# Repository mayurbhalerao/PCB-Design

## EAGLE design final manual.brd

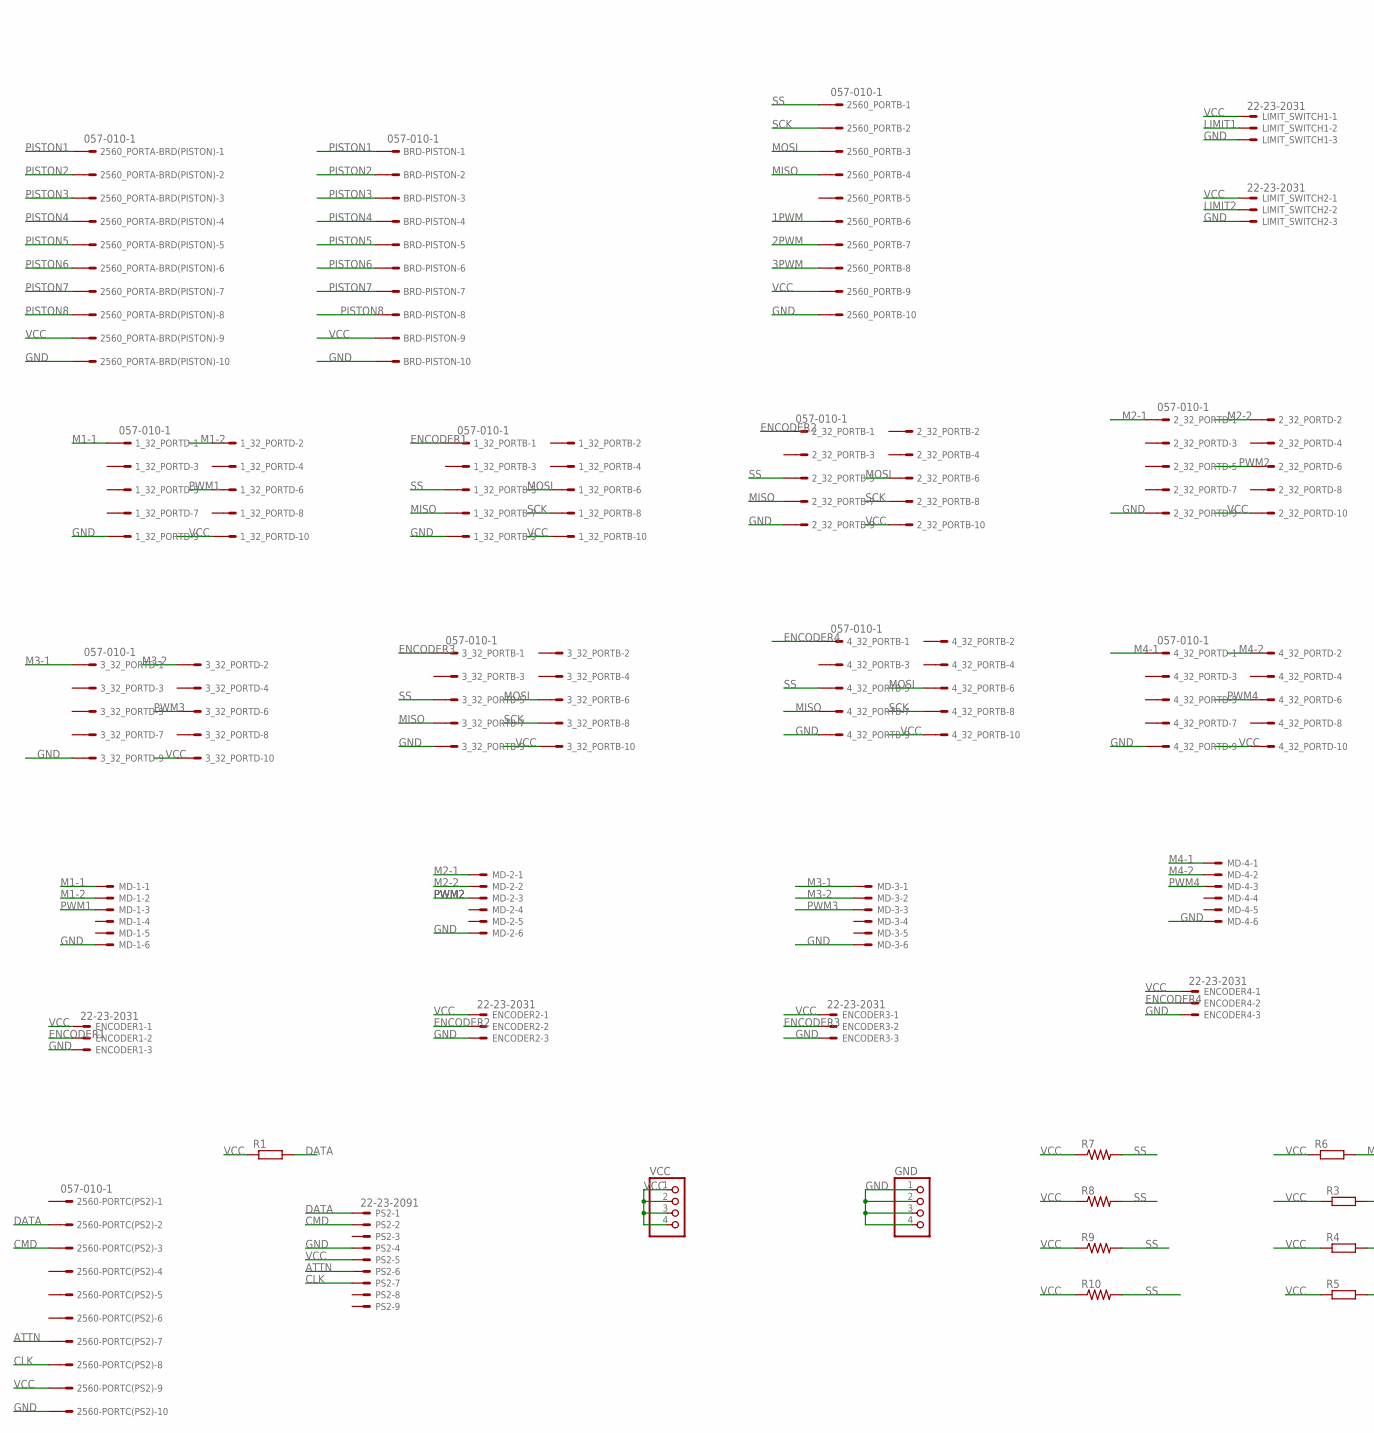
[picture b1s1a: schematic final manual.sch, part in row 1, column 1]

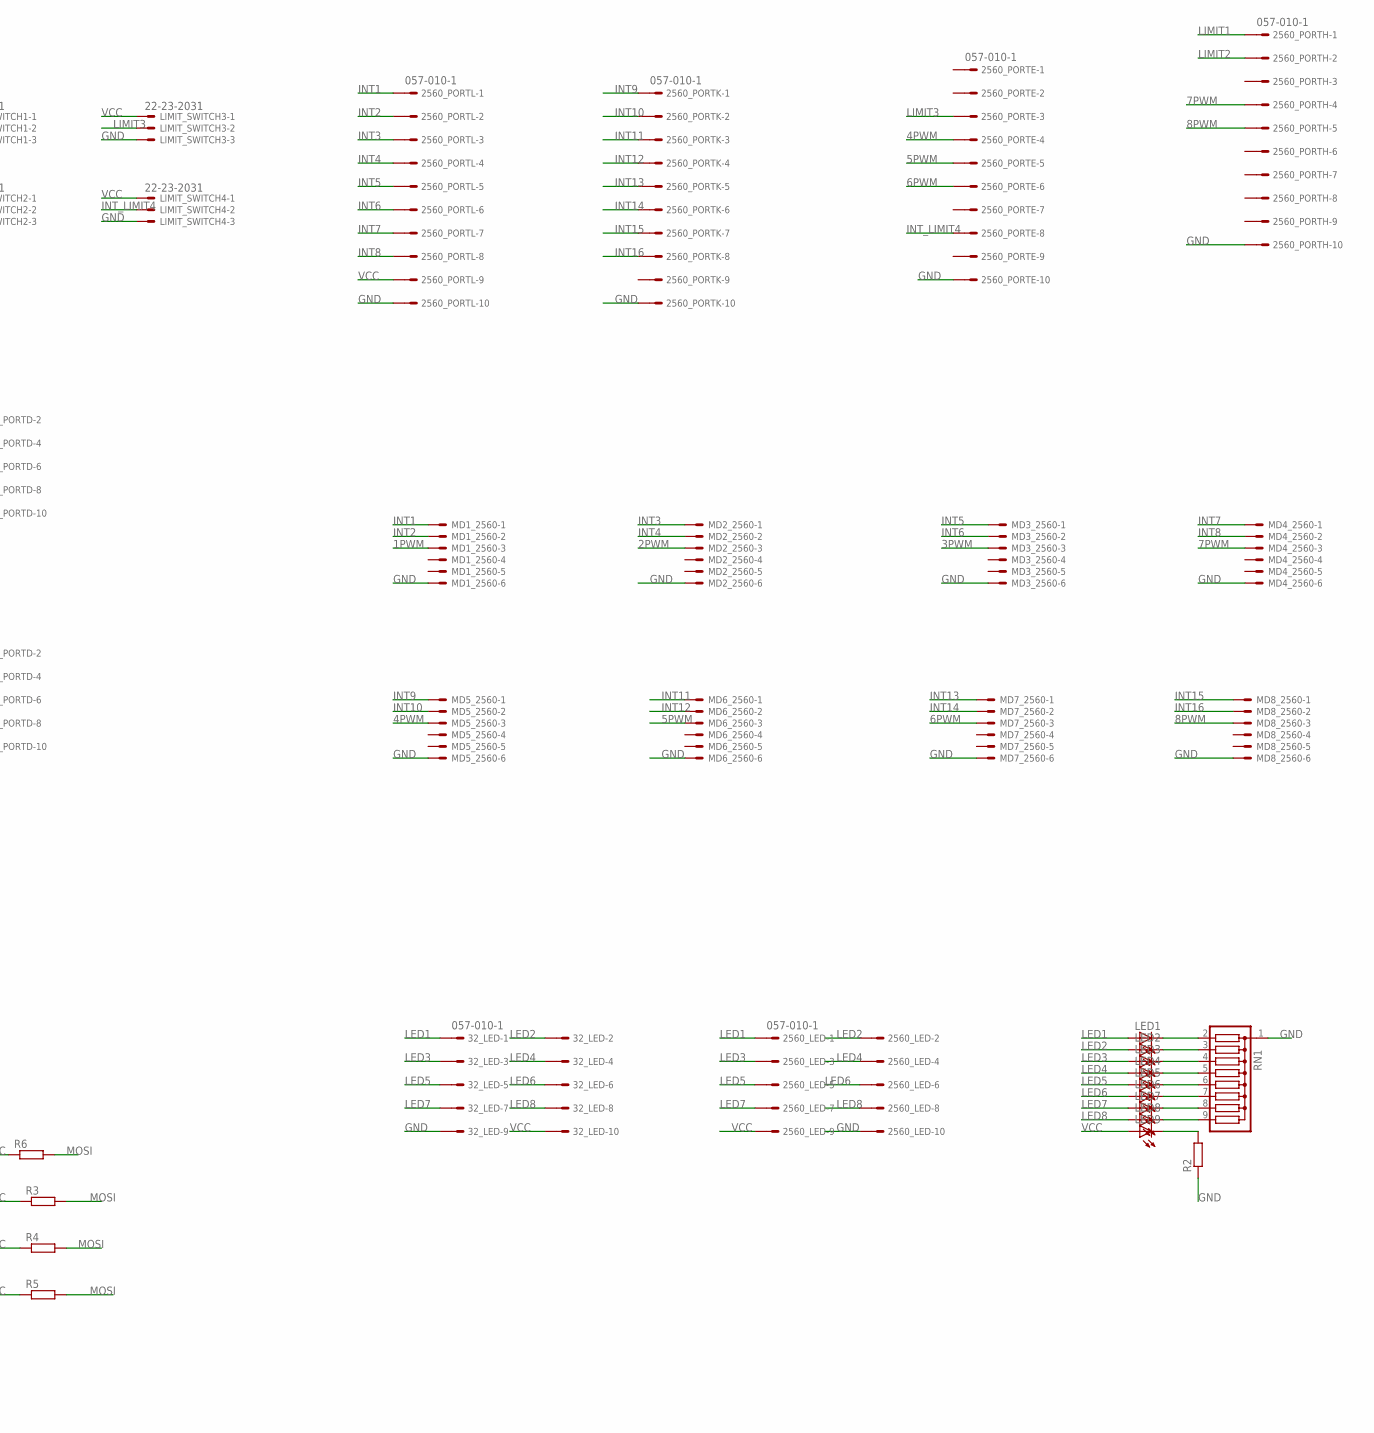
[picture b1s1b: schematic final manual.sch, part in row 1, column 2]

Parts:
1_32_PORTB, 1_32_PORTD, 2_32_PORTB, 2_32_PORTD, 3_32_PORTB, 3_32_PORTD, 4_32_PORTB, 4_32_PORTD, 32_LED, 2560-PORTC(PS2), 2560_LED, 2560_PORTA-BRD(PISTON), 2560_PORTB, 2560_PORTE, 2560_PORTH, 2560_PORTK, 2560_PORTL: 057-010-1
BRD-PISTON: 057-010-1
ENCODER1, ENCODER2, ENCODER3, ENCODER4: 22-23-2031
GND: PINHD-1X4; 1X04
LED1, LED2, LED3, LED4, LED5, LED6, LED7, LED8, LED9: LED3MM
LIMIT_SWITCH1, LIMIT_SWITCH2, LIMIT_SWITCH3, LIMIT_SWITCH4: 22-23-2031
MD1_2560, MD2_2560, MD3_2560, MD4_2560, MD5_2560, MD6_2560, MD7_2560, MD8_2560: 22-23-2061
MD-1, MD-2, MD-3, MD-4: 22-23-2061
PS2: 22-23-2091
R1, R2, R3, R4, R5, R6: R-EU_0204/7; 0204/7
R7, R8, R9, R10: R-US_0204/7; 0204/7
RN1: G08R; SIL9
VCC: PINHD-1X4; 1X04

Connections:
1PWM: 2560_PORTB.6, MD1_2560.3
2PWM: 2560_PORTB.7, MD2_2560.3
3PWM: 2560_PORTB.8, MD3_2560.3
4PWM: 2560_PORTE.4, MD5_2560.3
5PWM: 2560_PORTE.5, MD6_2560.3
6PWM: 2560_PORTE.6, MD7_2560.3
7PWM: 2560_PORTH.4, MD4_2560.3
8PWM: 2560_PORTH.5, MD8_2560.3
ATTN: 2560-PORTC(PS2).7, PS2.6
CLK: 2560-PORTC(PS2).8, PS2.7
CMD: 2560-PORTC(PS2).3, PS2.2
DATA: 2560-PORTC(PS2).2, PS2.1, R1.2
ENCODER1: 1_32_PORTB.1, ENCODER1.2
ENCODER2: 2_32_PORTB.1, ENCODER2.2
ENCODER3: 3_32_PORTB.1, ENCODER3.2
ENCODER4: 4_32_PORTB.1, ENCODER4.2
GND: 1_32_PORTB.9, 1_32_PORTD.9, 2_32_PORTB.9, 2_32_PORTD.9, 3_32_PORTB.9, 3_32_PORTD.9, 4_32_PORTB.9, 4_32_PORTD.9, 32_LED.9, 2560-PORTC(PS2).10, 2560_LED.10, 2560_PORTA-BRD(PISTON).10, 2560_PORTB.10, 2560_PORTE.10, 2560_PORTH.10, 2560_PORTK.10, 2560_PORTL.10, BRD-PISTON.10, ENCODER1.3, ENCODER2.3, ENCODER3.3, ENCODER4.3, GND.1, GND.2, GND.3, GND.4, LIMIT_SWITCH1.3, LIMIT_SWITCH2.3, LIMIT_SWITCH3.3, LIMIT_SWITCH4.3, MD1_2560.6, MD2_2560.6, MD3_2560.6, MD4_2560.6, MD5_2560.6, MD6_2560.6, MD7_2560.6, MD8_2560.6, MD-1.6, MD-2.6, MD-3.6, MD-4.6, PS2.4, R2.1, RN1.1
INT1: 2560_PORTL.1, MD1_2560.1
INT2: 2560_PORTL.2, MD1_2560.2
INT3: 2560_PORTL.3, MD2_2560.1
INT4: 2560_PORTL.4, MD2_2560.2
INT5: 2560_PORTL.5, MD3_2560.1
INT6: 2560_PORTL.6, MD3_2560.2
INT7: 2560_PORTL.7, MD4_2560.1
INT8: 2560_PORTL.8, MD4_2560.2
INT9: 2560_PORTK.1, MD5_2560.1
INT10: 2560_PORTK.2, MD5_2560.2
INT11: 2560_PORTK.3, MD6_2560.1
INT12: 2560_PORTK.4, MD6_2560.2
INT13: 2560_PORTK.5, MD7_2560.1
INT14: 2560_PORTK.6, MD7_2560.2
INT15: 2560_PORTK.7, MD8_2560.1
INT16: 2560_PORTK.8, MD8_2560.2
INT_LIMIT4: 2560_PORTE.8, LIMIT_SWITCH4.2
LED1: 32_LED.1, 2560_LED.1, LED1.A
LED2: 32_LED.2, 2560_LED.2, LED2.A
LED3: 32_LED.3, 2560_LED.3, LED3.A
LED4: 32_LED.4, 2560_LED.4, LED4.A
LED5: 32_LED.5, 2560_LED.5, LED5.A
LED6: 32_LED.6, 2560_LED.6, LED6.A
LED7: 32_LED.7, 2560_LED.7, LED7.A
LED8: 32_LED.8, 2560_LED.8, LED8.A
LIMIT1: 2560_PORTH.1, LIMIT_SWITCH1.2
LIMIT2: 2560_PORTH.2, LIMIT_SWITCH2.2
LIMIT3: 2560_PORTE.3, LIMIT_SWITCH3.2
M1-1: 1_32_PORTD.1, MD-1.1
M1-2: 1_32_PORTD.2, MD-1.2
M2-1: 2_32_PORTD.1, MD-2.1
M2-2: 2_32_PORTD.2, MD-2.2
M3-1: 3_32_PORTD.1, MD-3.1
M3-2: 3_32_PORTD.2, MD-3.2
M4-1: 4_32_PORTD.1, MD-4.1
M4-2: 4_32_PORTD.2, MD-4.2
MISO: 1_32_PORTB.7, 2_32_PORTB.7, 3_32_PORTB.7, 4_32_PORTB.7, 2560_PORTB.4
MOSI: 1_32_PORTB.6, 2_32_PORTB.6, 3_32_PORTB.6, 4_32_PORTB.6, 2560_PORTB.3, R3.2, R4.2, R5.2, R6.2
unnamed: LED1.K (C), RN1.2
unnamed: LED2.K (C), RN1.3
unnamed: LED3.K (C), RN1.4
unnamed: LED4.K (C), RN1.5
unnamed: LED5.K (C), RN1.6
unnamed: LED6.K (C), RN1.7
unnamed: LED7.K (C), RN1.8
unnamed: LED8.K (C), RN1.9
unnamed: LED9.K (C), R2.2
PISTON1: 2560_PORTA-BRD(PISTON).1, BRD-PISTON.1
PISTON2: 2560_PORTA-BRD(PISTON).2, BRD-PISTON.2
PISTON3: 2560_PORTA-BRD(PISTON).3, BRD-PISTON.3
PISTON4: 2560_PORTA-BRD(PISTON).4, BRD-PISTON.4
PISTON5: 2560_PORTA-BRD(PISTON).5, BRD-PISTON.5
PISTON6: 2560_PORTA-BRD(PISTON).6, BRD-PISTON.6
PISTON7: 2560_PORTA-BRD(PISTON).7, BRD-PISTON.7
PISTON8: 2560_PORTA-BRD(PISTON).8, BRD-PISTON.8
PWM1: 1_32_PORTD.6, MD-1.3
PWM2: 2_32_PORTD.6, MD-2.3
PWM3: 3_32_PORTD.6, MD-3.3
PWM4: 4_32_PORTD.6, MD-4.3
SCK: 1_32_PORTB.8, 2_32_PORTB.8, 3_32_PORTB.8, 4_32_PORTB.8, 2560_PORTB.2
SS: 1_32_PORTB.5, 2_32_PORTB.5, 3_32_PORTB.5, 4_32_PORTB.5, 2560_PORTB.1, R7.2, R8.2, R9.2, R10.2
VCC: 1_32_PORTB.10, 1_32_PORTD.10, 2_32_PORTB.10, 2_32_PORTD.10, 3_32_PORTB.10, 3_32_PORTD.10, 4_32_PORTB.10, 4_32_PORTD.10, 32_LED.10, 2560-PORTC(PS2).9, 2560_LED.9, 2560_PORTA-BRD(PISTON).9, 2560_PORTB.9, 2560_PORTL.9, BRD-PISTON.9, ENCODER1.1, ENCODER2.1, ENCODER3.1, ENCODER4.1, LED9.A, LIMIT_SWITCH1.1, LIMIT_SWITCH2.1, LIMIT_SWITCH3.1, LIMIT_SWITCH4.1, PS2.5, R1.1, R3.1, R4.1, R5.1, R6.1, R7.1, R8.1, R9.1, R10.1, VCC.1, VCC.2, VCC.3, VCC.4

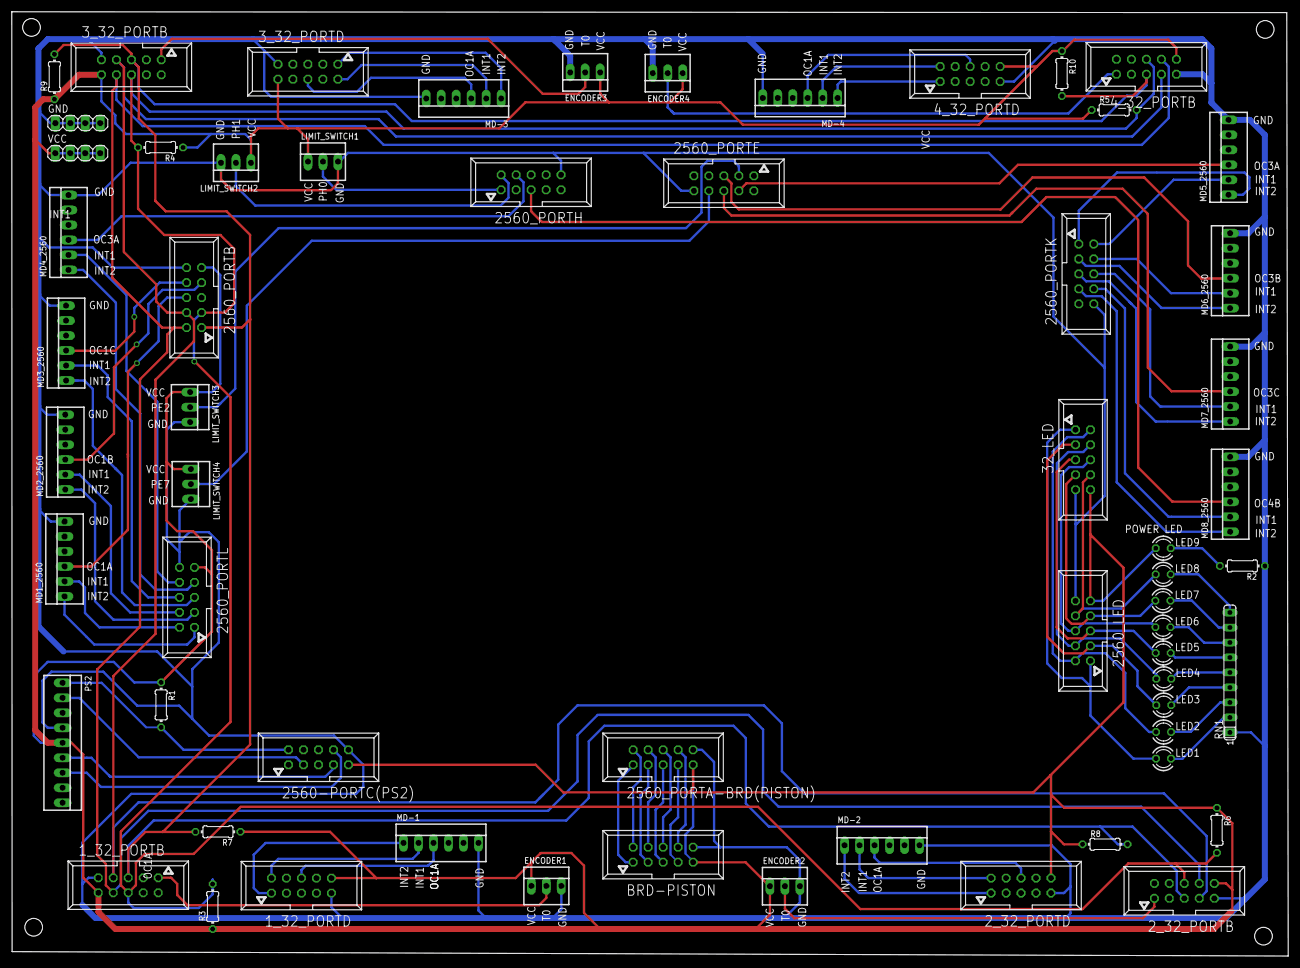
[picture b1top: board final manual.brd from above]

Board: 2 copper layers, 216.4 x 160.1 mm, 61 parts (0 on the bottom side), 79 nets.

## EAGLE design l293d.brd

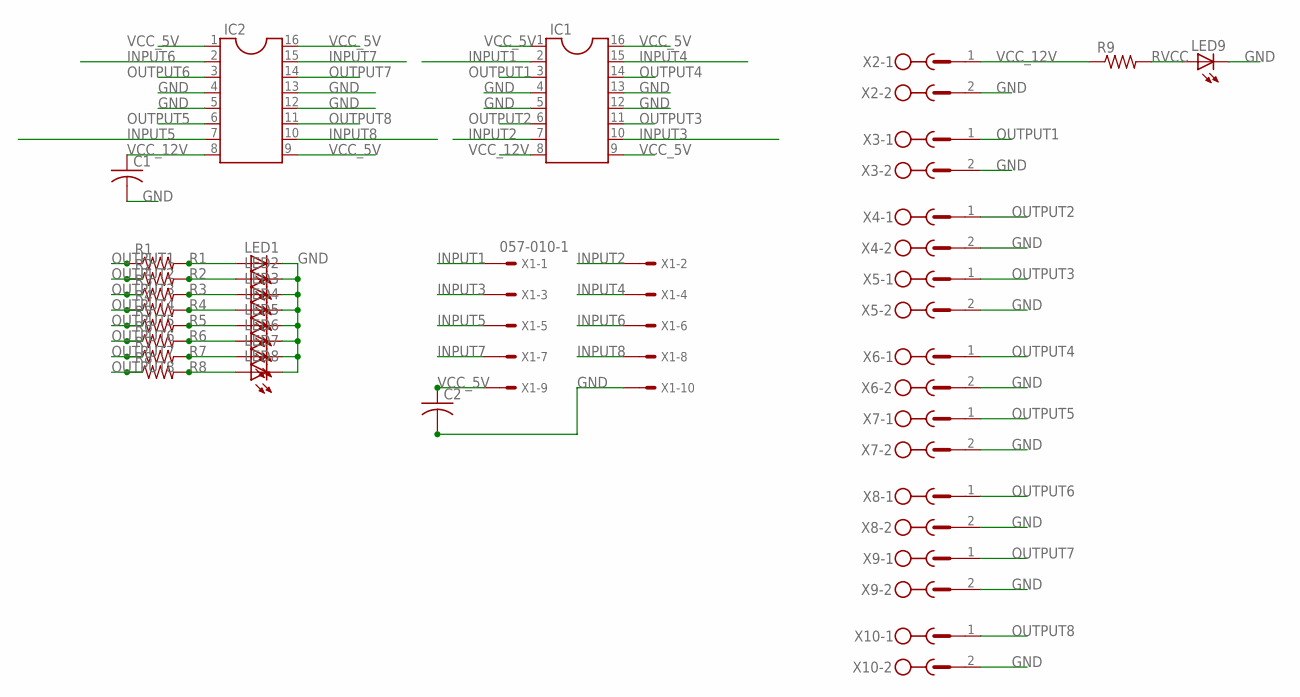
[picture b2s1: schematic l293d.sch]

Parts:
C1, C2: C-US050-025X075; C050-025X075
IC1, IC2: DIL16S; SOCKET-16
LED1, LED2, LED3, LED4, LED5, LED6, LED7, LED8, LED9: LED3MM
R1, R2, R3, R4, R5, R6, R7, R8, R9: R-US_0204/7; 0204/7
X1: 057-010-1
X2, X3, X4, X5, X6, X7, X8, X9, X10: MSTBV2

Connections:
GND: C1.2, C2.2, IC1.4, IC1.5, IC1.12, IC1.13, IC2.4, IC2.5, IC2.12, IC2.13, LED1.K (C), LED2.K (C), LED3.K (C), LED4.K (C), LED5.K (C), LED6.K (C), LED7.K (C), LED8.K (C), LED9.K (C), X1.10, X2.2, X3.2, X4.2, X5.2, X6.2, X7.2, X8.2, X9.2, X10.2
INPUT1: IC1.2, X1.1
INPUT2: IC1.7, X1.2
INPUT3: IC1.10, X1.3
INPUT4: IC1.15, X1.4
INPUT5: IC2.7, X1.5
INPUT6: IC2.2, X1.6
INPUT7: IC2.15, X1.7
INPUT8: IC2.10, X1.8
OUTPUT1: IC1.3, R1.1, X3.1
OUTPUT2: IC1.6, R2.1, X4.1
OUTPUT3: IC1.11, R3.1, X5.1
OUTPUT4: IC1.14, R4.1, X6.1
OUTPUT5: IC2.6, R5.1, X7.1
OUTPUT6: IC2.3, R6.1, X8.1
OUTPUT7: IC2.14, R7.1, X9.1
OUTPUT8: IC2.11, R8.1, X10.1
R1: LED1.A, R1.2
R2: LED2.A, R2.2
R3: LED3.A, R3.2
R4: LED4.A, R4.2
R5: LED5.A, R5.2
R6: LED6.A, R6.2
R7: LED7.A, R7.2
R8: LED8.A, R8.2
RVCC: LED9.A, R9.2
VCC_5V: C2.1, IC1.1, IC1.9, IC1.16, IC2.1, IC2.9, IC2.16, X1.9
VCC_12V: C1.1, IC1.8, IC2.8, R9.1, X2.1

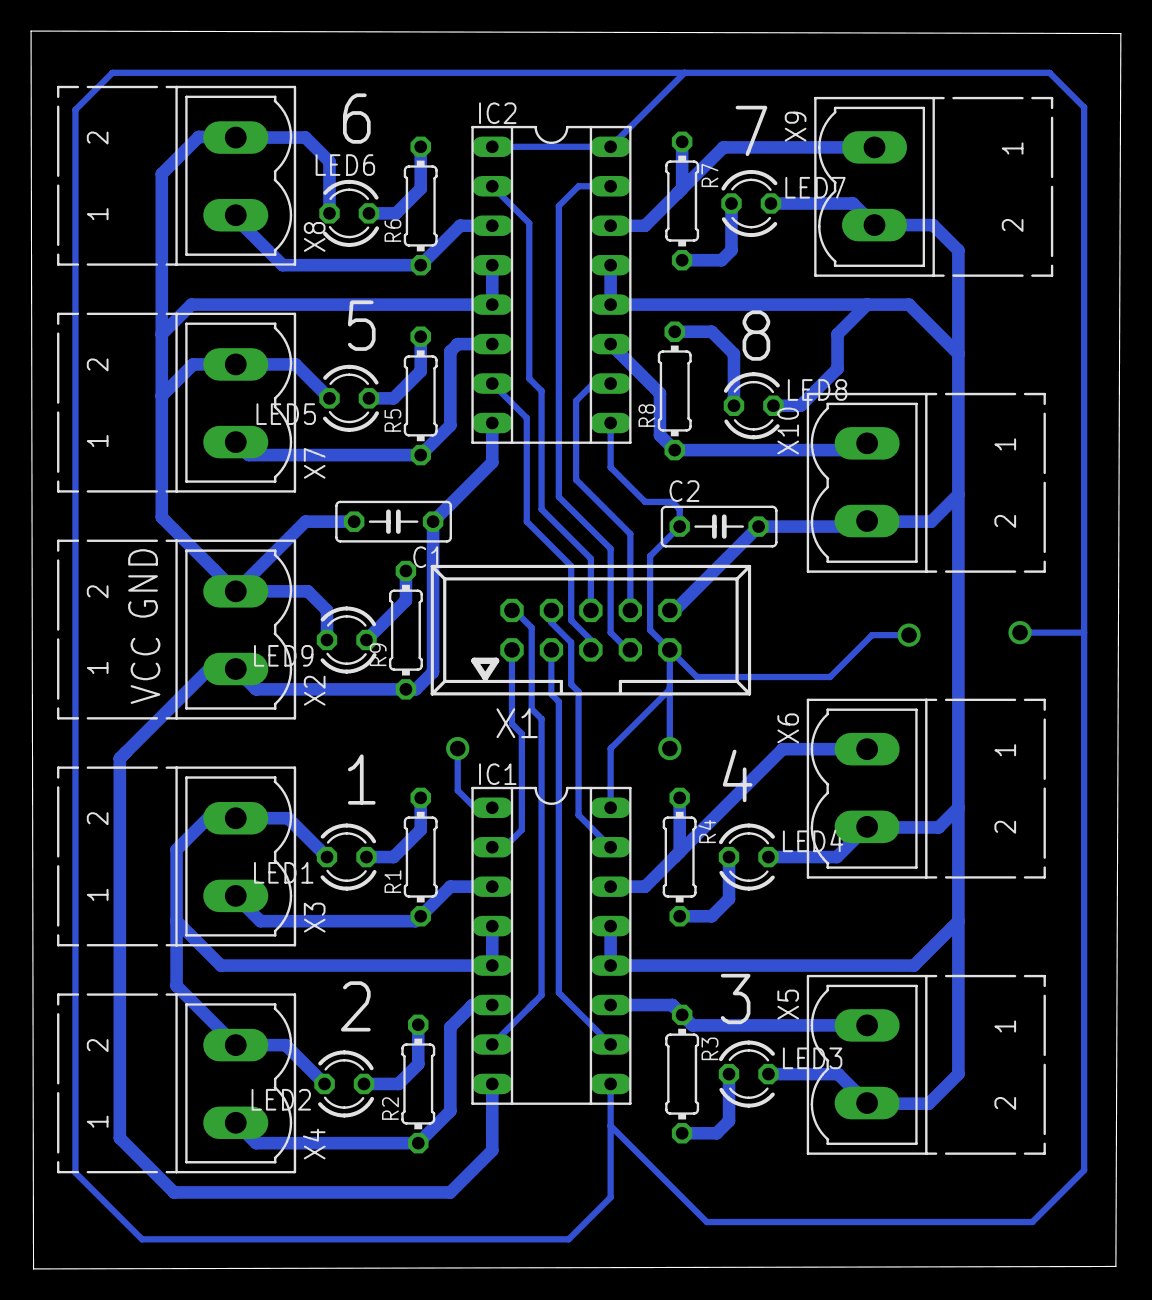
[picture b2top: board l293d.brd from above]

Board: 2 copper layers, 70.1 x 79.7 mm, 32 parts (0 on the bottom side), 28 nets.
